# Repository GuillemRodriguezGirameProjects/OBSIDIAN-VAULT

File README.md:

# OBSIDIAN-VAULT
Una repo amb totes els Vauls d'Obsidian per així no haver de pagar un duro per un programa que no sé si m'agradará

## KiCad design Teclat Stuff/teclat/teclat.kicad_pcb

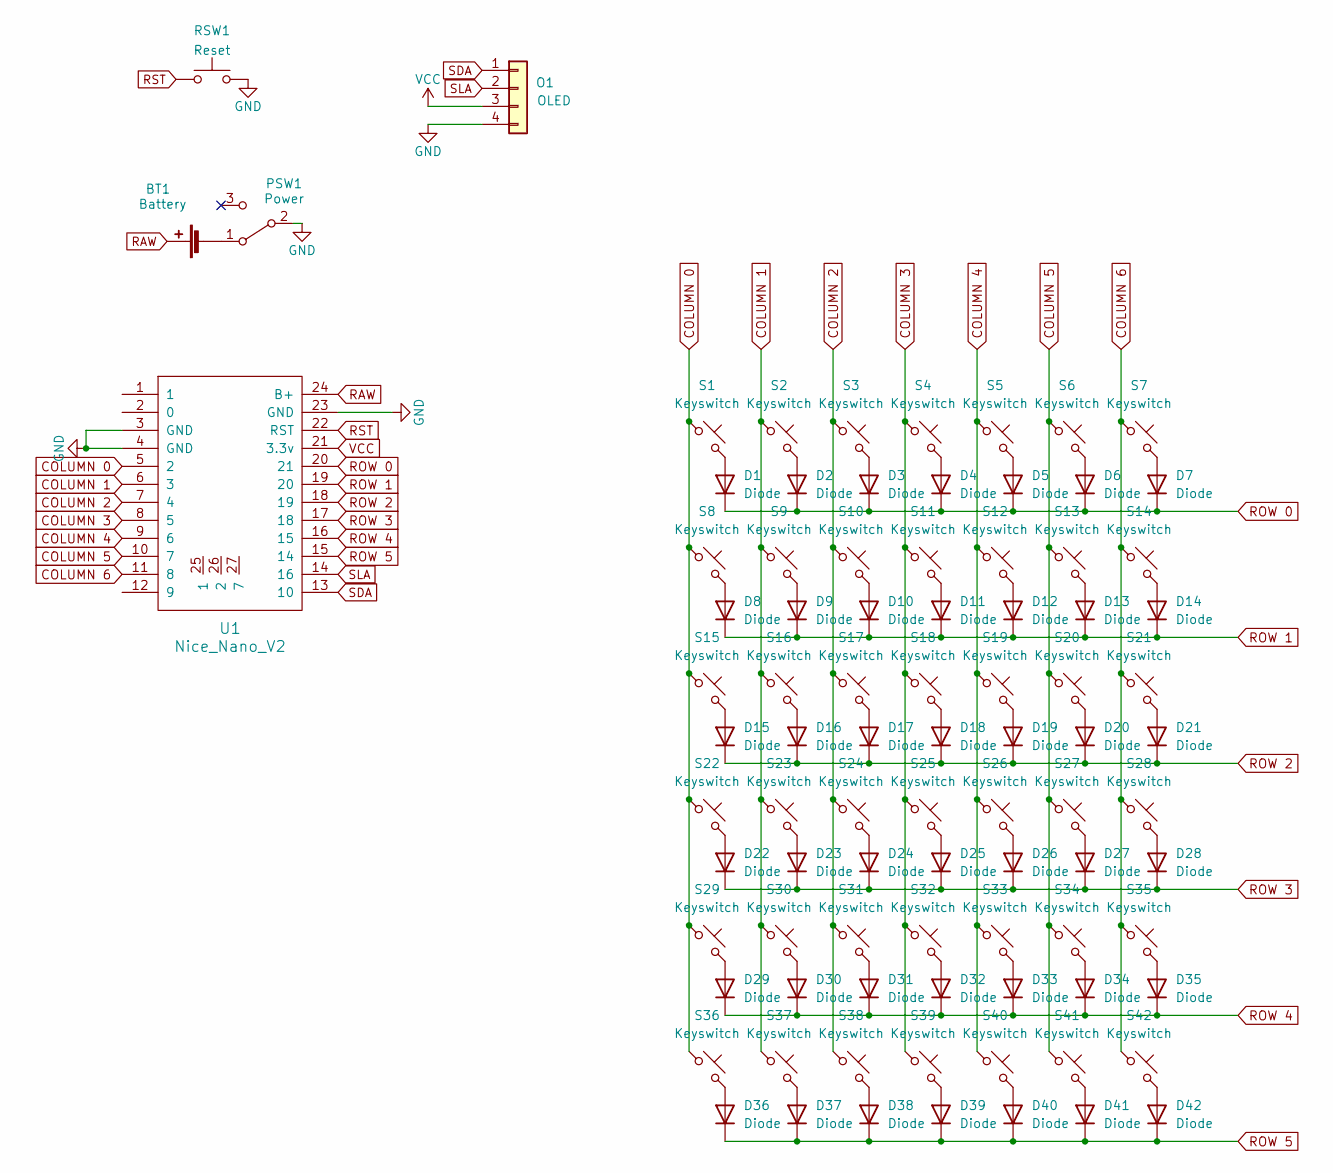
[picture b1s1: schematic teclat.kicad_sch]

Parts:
BT1: Battery; Battery_pads_reversible
D1, D2, D3, D4, D5, D6, D7, D8, D9, D10, D11, D12, D13, D14, D15, D16, D17, D18, D19, D20, D21, D22, D23, D24, D25, D26, D27, D28, D29, D30, D31, D32, D33, D34, D35, D36, D37, D38, D39, D40, D41, D42: Diode; Diode_DO-35
O1: OLED; OLED_jumpers
PSW1: Power
RSW1: Reset
S1, S2, S3, S4, S5, S6, S7, S8, S9, S10, S11, S12, S13, S14, S15, S16, S17, S18, S19, S20, S21, S22, S23, S24, S25, S26, S27, S28, S29, S30, S31, S32, S33, S34, S35, S36, S37, S38, S39, S40, S41, S42: Keyswitch; MX_PCB_1.00u
U1: Nice_Nano_V2

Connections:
COLUMN 0: S1.1, S8.1, S15.1, S22.1, S29.1, S36.1, U1.5 (2)
COLUMN 1: S2.1, S9.1, S16.1, S23.1, S30.1, S37.1, U1.6 (3)
COLUMN 2: S3.1, S10.1, S17.1, S24.1, S31.1, S38.1, U1.7 (4)
COLUMN 3: S4.1, S11.1, S18.1, S25.1, S32.1, S39.1, U1.8 (5)
COLUMN 4: S5.1, S12.1, S19.1, S26.1, S33.1, S40.1, U1.9 (6)
COLUMN 5: S6.1, S13.1, S20.1, S27.1, S34.1, S41.1, U1.10 (7)
COLUMN 6: S7.1, S14.1, S21.1, S28.1, S35.1, S42.1, U1.11 (8)
GND: O1.4, PSW1.2 (B), RSW1.2, U1.3 (GND), U1.4 (GND), U1.23 (GND)
unnamed: BT1.2 (-), PSW1.1 (A)
unnamed: D1.2 (A), S1.2
unnamed: D2.2 (A), S2.2
unnamed: D3.2 (A), S3.2
unnamed: D4.2 (A), S4.2
unnamed: D5.2 (A), S5.2
unnamed: D6.2 (A), S6.2
unnamed: D7.2 (A), S7.2
unnamed: D8.2 (A), S8.2
unnamed: D9.2 (A), S9.2
unnamed: D10.2 (A), S10.2
unnamed: D11.2 (A), S11.2
unnamed: D12.2 (A), S12.2
unnamed: D13.2 (A), S13.2
unnamed: D14.2 (A), S14.2
unnamed: D15.2 (A), S15.2
unnamed: D16.2 (A), S16.2
unnamed: D17.2 (A), S17.2
unnamed: D18.2 (A), S18.2
unnamed: D19.2 (A), S19.2
unnamed: D20.2 (A), S20.2
unnamed: D21.2 (A), S21.2
unnamed: D22.2 (A), S22.2
unnamed: D23.2 (A), S23.2
unnamed: D24.2 (A), S24.2
unnamed: D25.2 (A), S25.2
unnamed: D26.2 (A), S26.2
unnamed: D27.2 (A), S27.2
unnamed: D28.2 (A), S28.2
unnamed: D29.2 (A), S29.2
unnamed: D30.2 (A), S30.2
unnamed: D31.2 (A), S31.2
unnamed: D32.2 (A), S32.2
unnamed: D33.2 (A), S33.2
unnamed: D34.2 (A), S34.2
unnamed: D35.2 (A), S35.2
unnamed: D36.2 (A), S36.2
unnamed: D37.2 (A), S37.2
unnamed: D38.2 (A), S38.2
unnamed: D39.2 (A), S39.2
unnamed: D40.2 (A), S40.2
unnamed: D41.2 (A), S41.2
unnamed: D42.2 (A), S42.2
RAW: BT1.1 (+), U1.24 (B+)
ROW 0: D1.1 (K), D2.1 (K), D3.1 (K), D4.1 (K), D5.1 (K), D6.1 (K), D7.1 (K), U1.20 (21)
ROW 1: D8.1 (K), D9.1 (K), D10.1 (K), D11.1 (K), D12.1 (K), D13.1 (K), D14.1 (K), U1.19 (20)
ROW 2: D15.1 (K), D16.1 (K), D17.1 (K), D18.1 (K), D19.1 (K), D20.1 (K), D21.1 (K), U1.18 (19)
ROW 3: D22.1 (K), D23.1 (K), D24.1 (K), D25.1 (K), D26.1 (K), D27.1 (K), D28.1 (K), U1.17 (18)
ROW 4: D29.1 (K), D30.1 (K), D31.1 (K), D32.1 (K), D33.1 (K), D34.1 (K), D35.1 (K), U1.16 (15)
ROW 5: D36.1 (K), D37.1 (K), D38.1 (K), D39.1 (K), D40.1 (K), D41.1 (K), D42.1 (K), U1.15 (14)
RST: RSW1.1, U1.22 (RST)
SDA: O1.1, U1.13 (10)
SLA: O1.2, U1.14 (16)
VCC: U1.21 (3.3v)

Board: 2 copper layers, 85 parts (0 on the bottom side), 56 nets, no tracks yet.

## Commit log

2024-04-01 copia-pega del Vault que tenia d'obsidian
2024-04-01 asdfç
2024-04-07 Push d'alguns cambis en la documentació del teclat
    Push amb canvis en la documentació del teclat i amb la primera plantilla de KiCad per provar a dissenyar junt amb la plantilla que estic fent servir com a exemple per fer la meva
2024-04-08 Es fa una llista de videos referencia pel teclat.
2024-12-01 Canvis que no recordo que vaig fer
